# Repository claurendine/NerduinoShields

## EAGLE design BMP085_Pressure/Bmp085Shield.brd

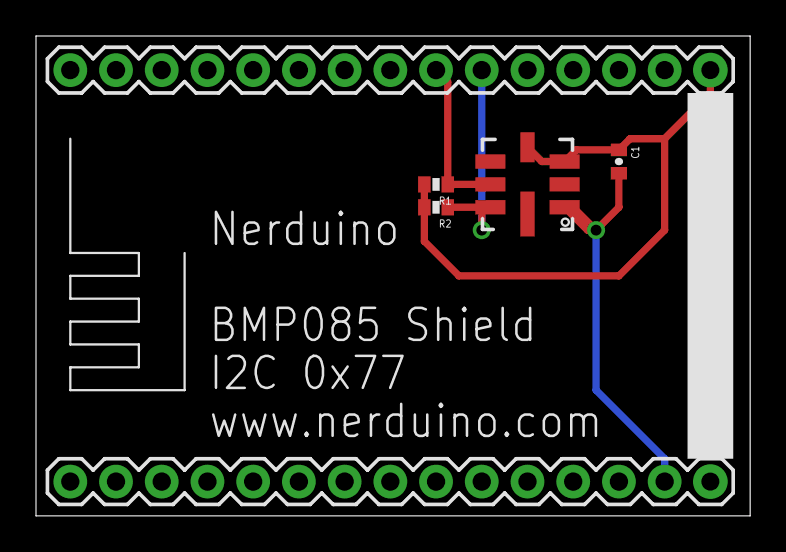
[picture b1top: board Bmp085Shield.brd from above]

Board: 2 copper layers, 39.7 x 26.7 mm, 5 parts (0 on the bottom side), 4 nets.

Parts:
C1: 0.1uF; 0402-CAP
R1, R2: 4.7k; 0402-RES
U$1: NERDSHIELD; NERDUINO_STACK
U$2: BMP085

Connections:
3.3V: C1.1, R1.2, R2.2, U$1.16, U$2.3, U$2.4
GND: C1.2, U$1.14, U$2.1
unnamed: R2.1, U$1.21, U$2.7
unnamed: R1.1, U$1.22, U$2.6

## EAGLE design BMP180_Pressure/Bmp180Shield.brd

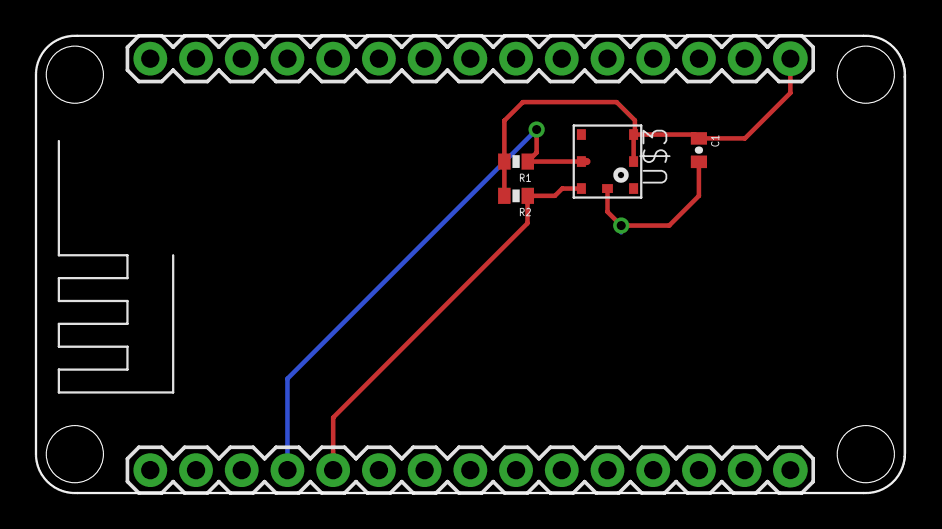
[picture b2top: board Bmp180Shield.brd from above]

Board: 2 copper layers, 48.3 x 25.4 mm, 5 parts (0 on the bottom side), 4 nets.

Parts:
C1: 0.1uF; 0402-CAP
R1, R2: 4.7k; 0402-RES
U$1: NERDSHIELD; NERDUINO_STACK
U$3: BMP180

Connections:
3.3V: C1.1, R1.2, R2.2, U$1.16, U$3.2, U$3.3
GND: C1.2, U$1.10, U$1.14, U$1.17, U$3.7
unnamed: R2.1, U$1.5, U$3.6
unnamed: R1.1, U$1.4, U$3.5

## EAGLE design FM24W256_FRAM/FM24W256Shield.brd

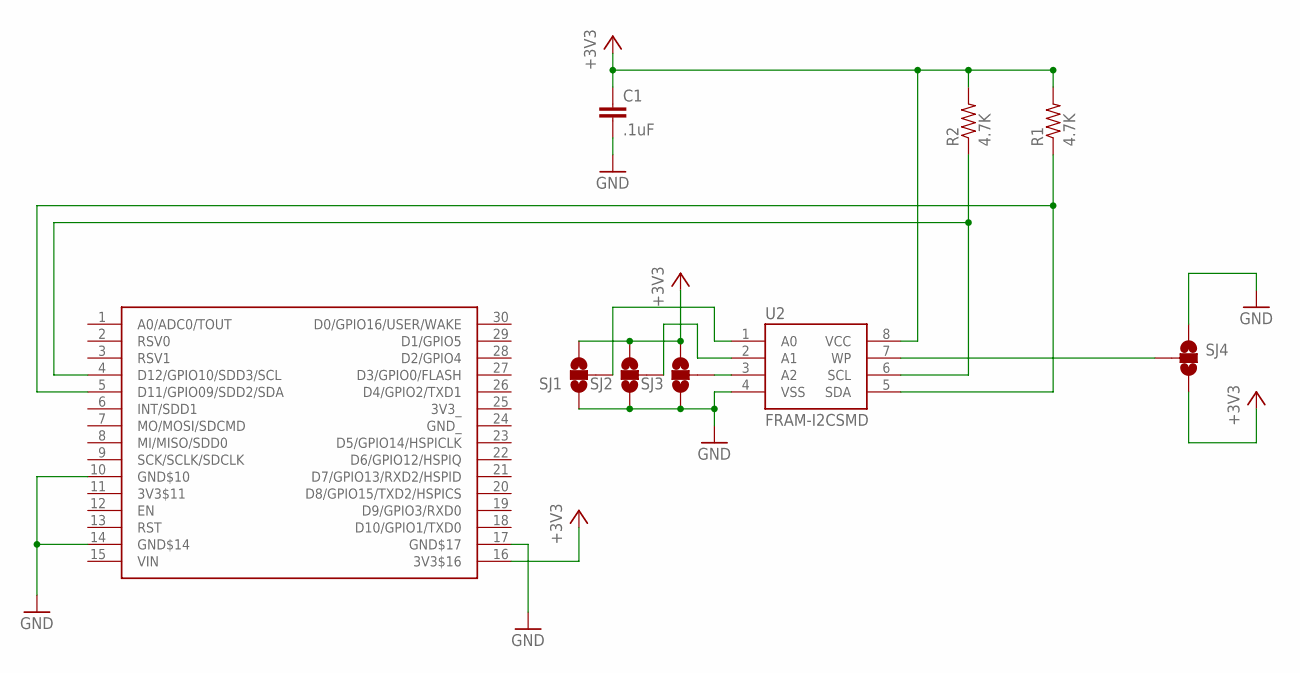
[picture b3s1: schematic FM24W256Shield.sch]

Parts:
C1: .1uF; 0603-CAP
R1, R2: 4.7K; 0603-RES
SJ1, SJ2, SJ3, SJ4: SOLDERJUMPER_2WAYPASTE1&2; SJ_3_PASTE1&2
U2: FRAM-I2CSMD; SO08
U$2: NERDSHIELD; NERDUINO_STACK

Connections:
+3V3: C1.1, R1.2, R2.2, SJ1.3, SJ2.3, SJ3.3, SJ4.3, U2.8 (VCC), U$2.16 (3V3$16)
GND: C1.2, SJ1.1, SJ2.1, SJ3.1, SJ4.1, U2.4 (VSS), U$2.10 (GND$10), U$2.14 (GND$14), U$2.17 (GND$17)
unnamed: R1.1, U2.5 (SDA), U$2.5 (D11/GPIO09/SDD2/SDA)
unnamed: SJ3.2, U2.3 (A2)
unnamed: R2.1, U2.6 (SCL), U$2.4 (D12/GPIO10/SDD3/SCL)
unnamed: SJ2.2, U2.2 (A1)
unnamed: SJ1.2, U2.1 (A0)
unnamed: SJ4.2, U2.7 (WP)

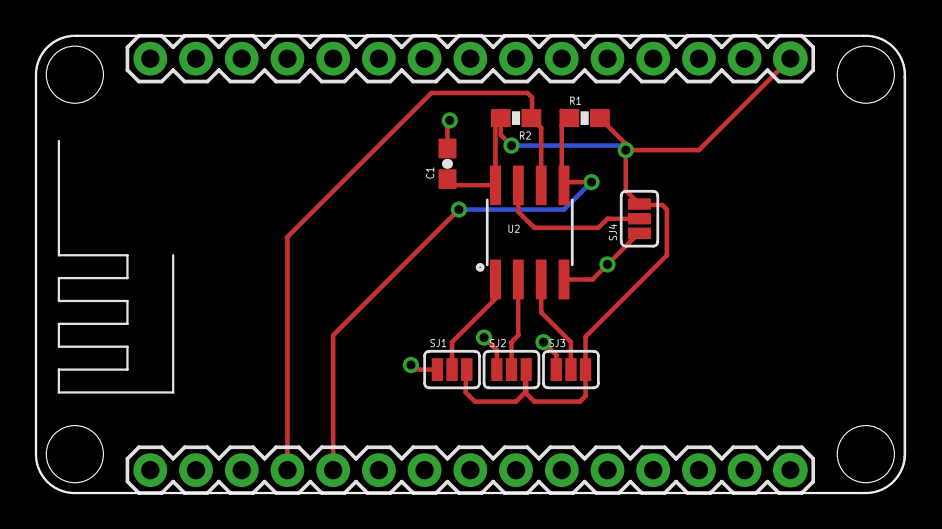
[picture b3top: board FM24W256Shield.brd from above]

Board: 2 copper layers, 48.3 x 25.4 mm, 9 parts (0 on the bottom side), 8 nets.

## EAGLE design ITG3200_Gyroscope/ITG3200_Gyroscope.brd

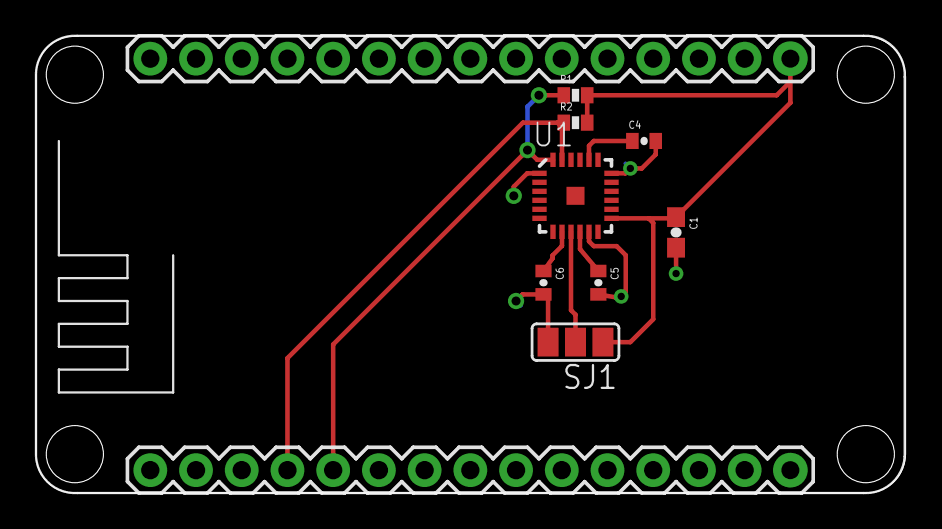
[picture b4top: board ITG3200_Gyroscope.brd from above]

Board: 2 copper layers, 48.3 x 25.4 mm, 9 parts (0 on the bottom side), 8 nets.

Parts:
C1: .1uF; 0603-CAP
C4: 2.2nF; 0402-CAP
C5: .1uF; 0402-CAP
C6: 10nF; 0402-CAP
R1, R2: 4.7K; 0402-RES
SJ1: SJ_2
U1: ITG-3200; QFN-24
U$2: NERDSHIELD; NERDUINO_STACK

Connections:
+3V3: C1.1, R1.2, R2.2, SJ1.1, U1.13, U$2.16
GND: C1.2, C4.2, C5.2, C6.2, SJ1.3, U1.1, U1.11, U1.18, U$2.10, U$2.14, U$2.17
unnamed: SJ1.2, U1.9
unnamed: R1.1, U1.24, U$2.5
unnamed: R2.1, U1.23, U$2.4
unnamed: C4.1, U1.20
unnamed: C5.1, U1.10
unnamed: C6.1, U1.8

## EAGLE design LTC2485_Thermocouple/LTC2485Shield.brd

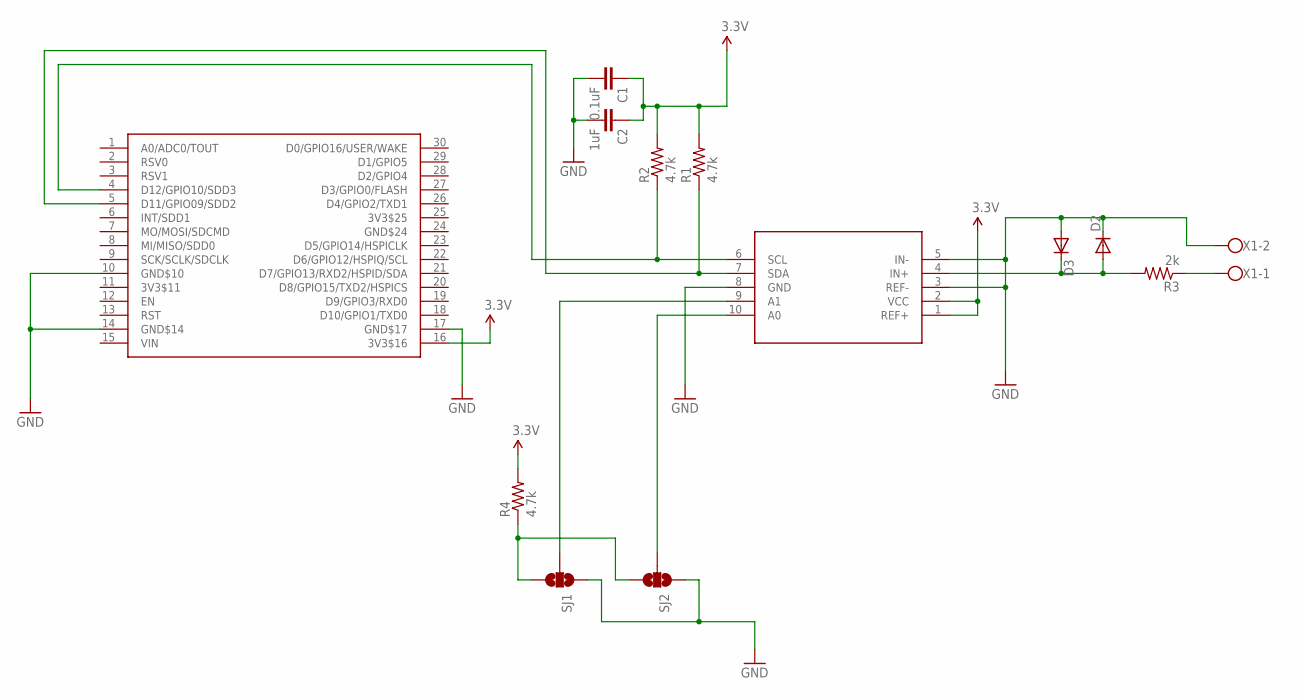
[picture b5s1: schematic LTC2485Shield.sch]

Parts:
C1: 0.1uF; 0402-CAP
C2: 1uF; 0402-CAP
D2, D3: DIODESOD; SOD-323
R1, R2, R4: 4.7k; 0402-RES
R3: 2k; 0402-RES
SJ1, SJ2: SOLDERJUMPER_2WAYT; SJ_2
U$1: NERDSHIELD; NERDUINO_STACK
U$2: LTC2485; DFN10-3X3
X1: W237-102

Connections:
3.3V: C1.1, C2.1, R1.2, R2.2, R4.2, U$1.16 (3V3$16), U$2.1 (REF+), U$2.2 (VCC)
GND: C1.2, C2.2, D2.1 (C), D3.2 (A), SJ1.1, SJ2.1, U$1.10 (GND$10), U$1.14 (GND$14), U$1.17 (GND$17), U$2.3 (REF-), U$2.5 (IN-), U$2.8 (GND), X1.2
unnamed: R3.1, X1.1
unnamed: R1.1, U$1.5 (D11/GPIO09/SDD2), U$2.7 (SDA)
unnamed: D2.2 (A), D3.1 (C), R3.2, U$2.4 (IN+)
unnamed: R4.1, SJ1.3, SJ2.3
unnamed: SJ1.2, U$2.9 (A1)
unnamed: R2.1, U$1.4 (D12/GPIO10/SDD3), U$2.6 (SCL)
unnamed: SJ2.2, U$2.10 (A0)

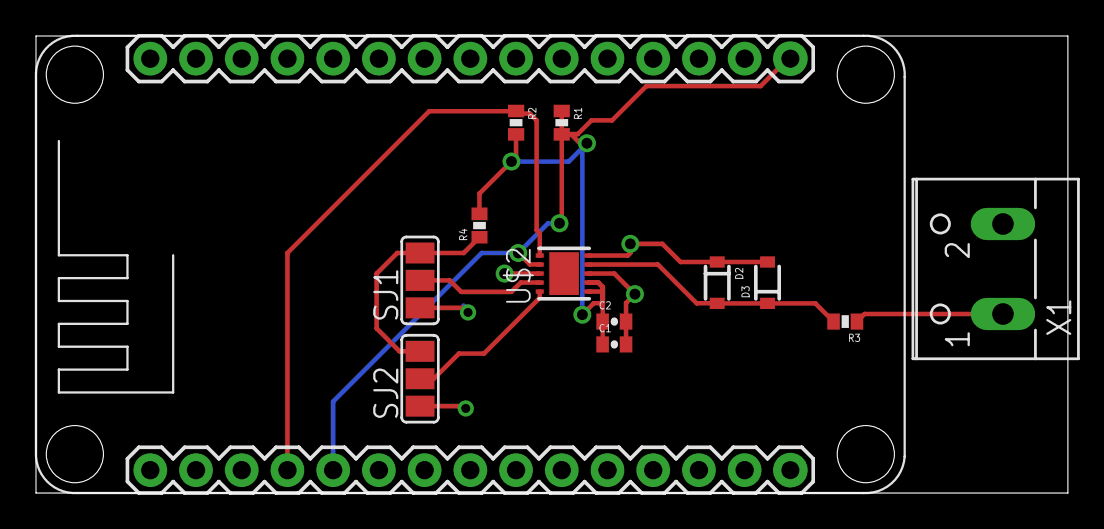
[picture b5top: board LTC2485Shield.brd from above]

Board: 2 copper layers, 57.3 x 25.4 mm, 13 parts (0 on the bottom side), 9 nets.

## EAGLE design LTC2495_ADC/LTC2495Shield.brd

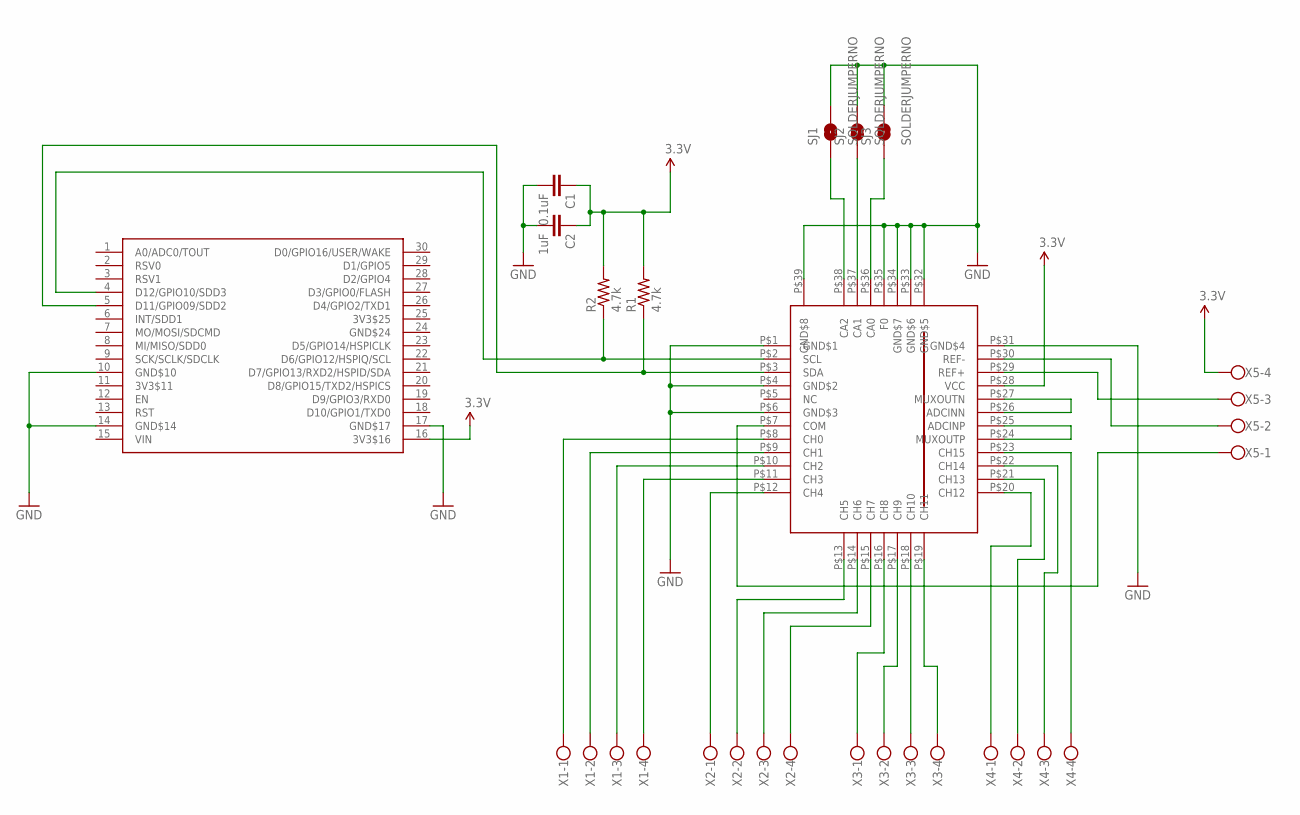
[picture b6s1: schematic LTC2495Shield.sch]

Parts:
C1: 0.1uF; 0402-CAP
C2: 1uF; 0402-CAP
R1, R2: 4.7k; 0402-RES
SJ1, SJ2, SJ3: SOLDERJUMPERNO; SJ_2S-NO
U$1: NERDSHIELD; NERDUINO_STACK
U$3: LTC2495; UHF38
X1, X2, X3, X4, X5: W237-4

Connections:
3.3V: C1.1, C2.1, R1.2, R2.2, U$1.16 (3V3$16), U$3.P$28 (VCC), X5.4
GND: C1.2, C2.2, SJ1.2, SJ2.2, SJ3.2, U$1.10 (GND$10), U$1.14 (GND$14), U$1.17 (GND$17), U$3.P$1 (GND$1), U$3.P$4 (GND$2), U$3.P$6 (GND$3), U$3.P$31 (GND$4), U$3.P$32 (GND$5), U$3.P$33 (GND$6), U$3.P$34 (GND$7), U$3.P$35 (F0), U$3.P$39 (GND$8)
unnamed: R1.1, U$1.5 (D11/GPIO09/SDD2), U$3.P$3 (SDA)
unnamed: U$3.P$8 (CH0), X1.1
unnamed: U$3.P$9 (CH1), X1.2
unnamed: U$3.P$10 (CH2), X1.3
unnamed: U$3.P$11 (CH3), X1.4
unnamed: U$3.P$12 (CH4), X2.1
unnamed: R2.1, U$1.4 (D12/GPIO10/SDD3), U$3.P$2 (SCL)
unnamed: U$3.P$13 (CH5), X2.2
unnamed: U$3.P$14 (CH6), X2.3
unnamed: U$3.P$15 (CH7), X2.4
unnamed: U$3.P$16 (CH8), X3.1
unnamed: U$3.P$17 (CH9), X3.2
unnamed: U$3.P$18 (CH10), X3.3
unnamed: U$3.P$19 (CH11), X3.4
unnamed: U$3.P$20 (CH12), X4.1
unnamed: U$3.P$21 (CH13), X4.2
unnamed: U$3.P$22 (CH14), X4.3
unnamed: U$3.P$23 (CH15), X4.4
unnamed: SJ1.1, U$3.P$38 (CA2)
unnamed: SJ2.1, U$3.P$37 (CA1)
unnamed: SJ3.1, U$3.P$36 (CA0)
unnamed: U$3.P$7 (COM), X5.1
unnamed: U$3.P$29 (REF+), X5.3
unnamed: U$3.P$30 (REF-), X5.2
unnamed: U$3.P$26 (ADCINN), U$3.P$27 (MUXOUTN)
unnamed: U$3.P$24 (MUXOUTP), U$3.P$25 (ADCINP)

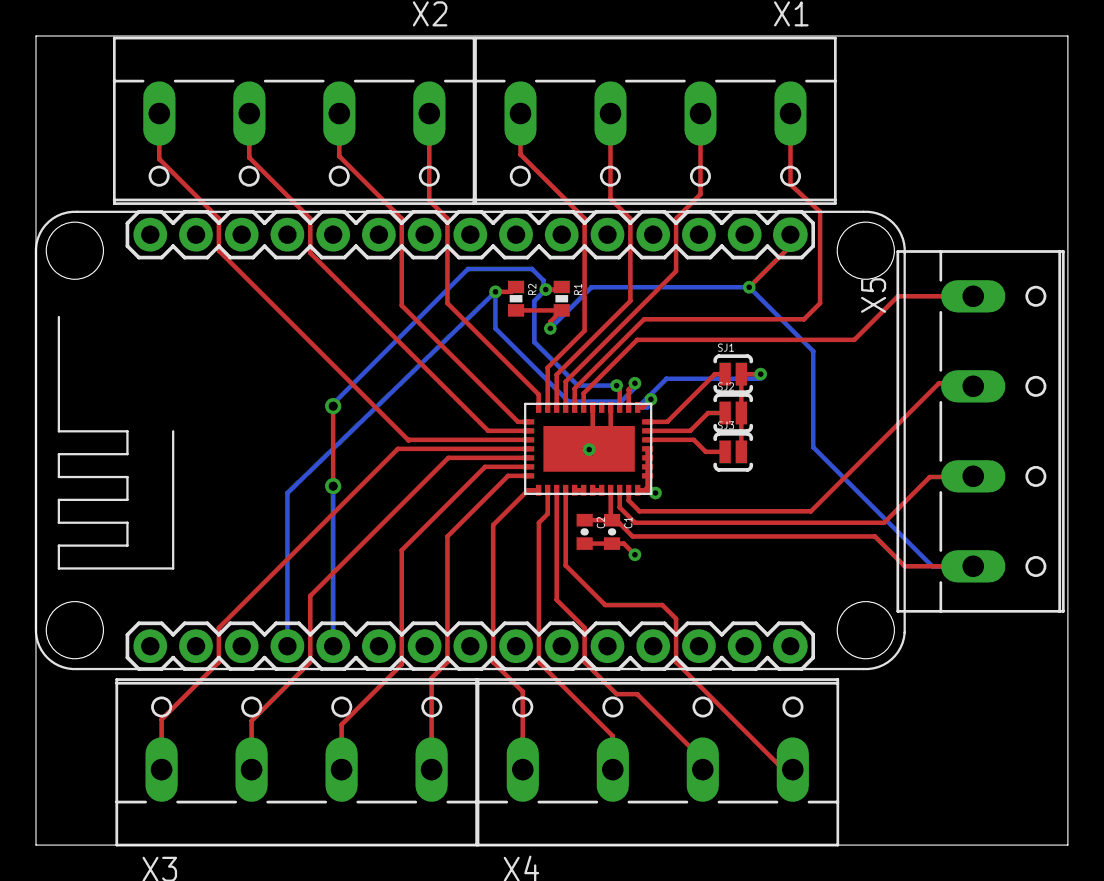
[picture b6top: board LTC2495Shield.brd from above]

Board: 2 copper layers, 57.3 x 44.9 mm, 14 parts (0 on the bottom side), 28 nets.

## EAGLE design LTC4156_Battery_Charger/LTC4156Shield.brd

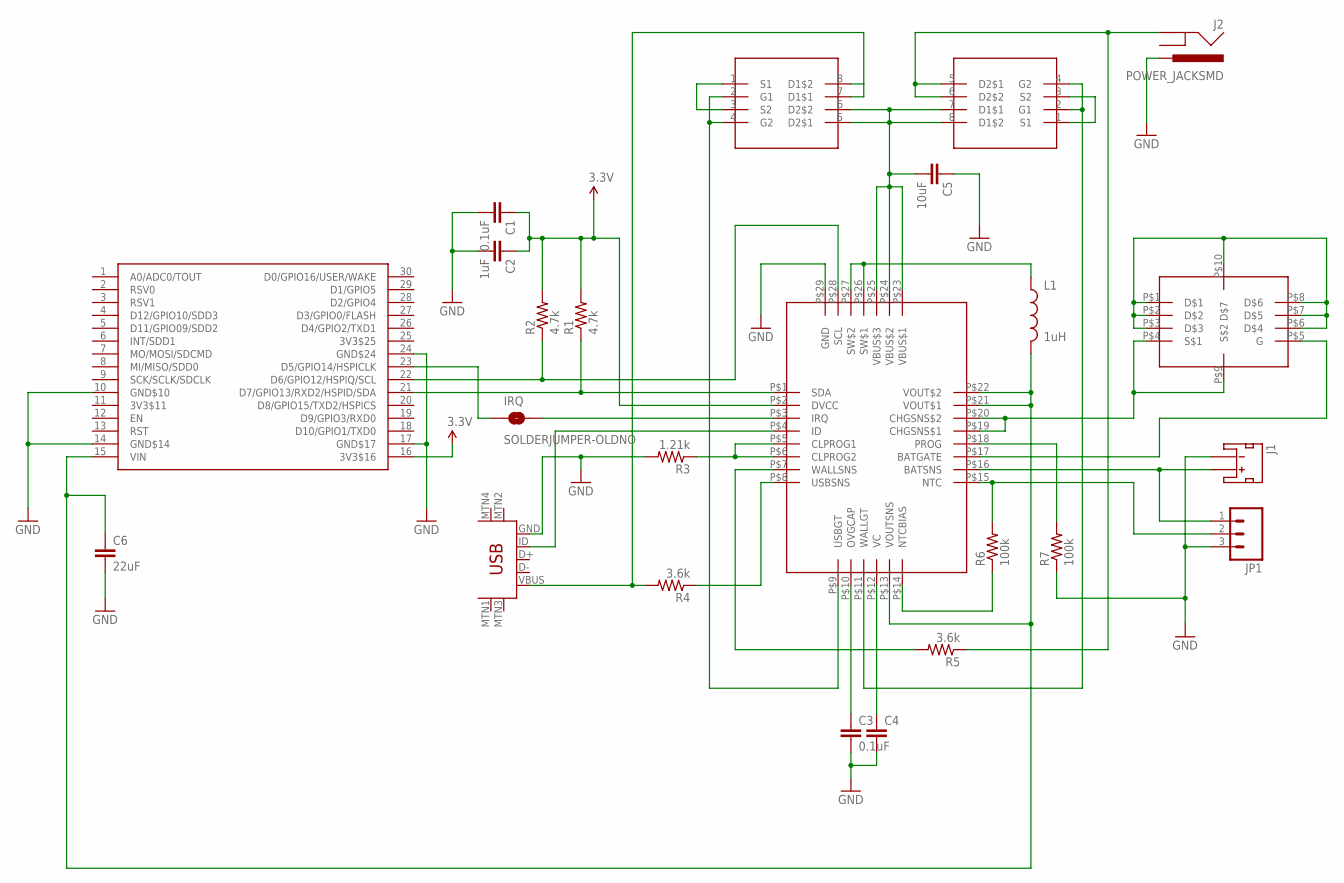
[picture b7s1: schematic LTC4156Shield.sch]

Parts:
C1, C3: 0.1uF; 0402-CAP
C2: 1uF; 0402-CAP
C4: CAP0805; 0805
C5: 10uF; 0402-CAP
C6: 22uF; 0402-CAP
IRQ: SOLDERJUMPER-OLDNO; SJ_2S-NO
J1: JST_2MM_MALE; JST-2-SMD
J2: POWER_JACKSMD; POWER_JACK_SMD
JP1: M03; JST-3-SMD
L1: 1uH; 0805
R1, R2: 4.7k; 0402-RES
R3: 1.21k; 0402-RES
R4, R5: 3.6k; 0402-RES
R6, R7: 100k; 0402-RES
U$1: NERDSHIELD; NERDUINO_STACK
U$2: LTC4156; QFN28
U$3, U$5: SI7938DP; SO08
U$4: USB-MINIB-5PIN; USB-MINIB
U$6: SI5481

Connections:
3.3V: C1.1, C2.1, R1.2, R2.2, U$1.16 (3V3$16), U$2.P$2 (DVCC)
GND: C1.2, C2.2, C3.2, C4.2, C5.1, C6.2, J1.1 (-), J2.VIN0 (PWR), JP1.3, R3.2, R7.1, U$1.10 (GND$10), U$1.14 (GND$14), U$1.17 (GND$17), U$1.24 (GND$24), U$2.P$29 (GND), U$4.GND
unnamed: R4.1, U$2.P$8 (USBSNS)
unnamed: R1.1, U$1.21 (D7/GPIO13/RXD2/HSPID/SDA), U$2.P$1 (SDA)
unnamed: IRQ.2, U$2.P$3 (IRQ)
unnamed: R3.1, U$2.P$5 (CLPROG1), U$2.P$6 (CLPROG2)
unnamed: IRQ.1, U$1.23 (D5/GPIO14/HSPICLK)
unnamed: U$2.P$4 (ID), U$4.ID
unnamed: R4.2, U$3.7 (D1$1), U$3.8 (D1$2), U$4.VBUS
unnamed: R2.1, U$1.22 (D6/GPIO12/HSPIQ/SCL), U$2.P$28 (SCL)
unnamed: U$2.P$9_ (USBGT), U$3.2 (G1), U$3.4 (G2)
unnamed: C5.2, U$2.P$23 (VBUS$1), U$2.P$24 (VBUS$2), U$2.P$25 (VBUS$3), U$3.5 (D2$1), U$3.6 (D2$2), U$5.7 (D1$1), U$5.8 (D1$2)
unnamed: R5.2, U$2.P$7 (WALLSNS)
unnamed: U$3.1 (S1), U$3.3 (S2)
unnamed: U$5.1 (S1), U$5.3 (S2)
unnamed: U$2.P$11_ (WALLGT), U$5.2 (G1), U$5.4 (G2)
unnamed: J2.P$4 (GND), R5.1, U$5.5 (D2$1), U$5.6 (D2$2)
unnamed: C3.1, U$2.P$10_ (OVGCAP)
unnamed: C4.1, U$2.P$12_ (VC)
unnamed: C6.1, L1.2, U$1.15 (VIN), U$2.P$13_ (VOUTSNS), U$2.P$21 (VOUT$1), U$2.P$22 (VOUT$2)
unnamed: J1.2 (+), JP1.1, U$2.P$16 (BATSNS)
unnamed: L1.1, U$2.P$26 (SW$1), U$2.P$27 (SW$2)
unnamed: JP1.2, R6.2, U$2.P$15 (NTC)
unnamed: R6.1, U$2.P$14_ (NTCBIAS)
unnamed: U$2.P$17 (BATGATE), U$6.P$5 (G)
unnamed: U$2.P$19 (CHGSNS$1), U$2.P$20 (CHGSNS$2), U$6.P$4, U$6.P$9
unnamed: U$6.P$1, U$6.P$2, U$6.P$3, U$6.P$6, U$6.P$7, U$6.P$8, U$6.P$10
unnamed: R7.2, U$2.P$18 (PROG)

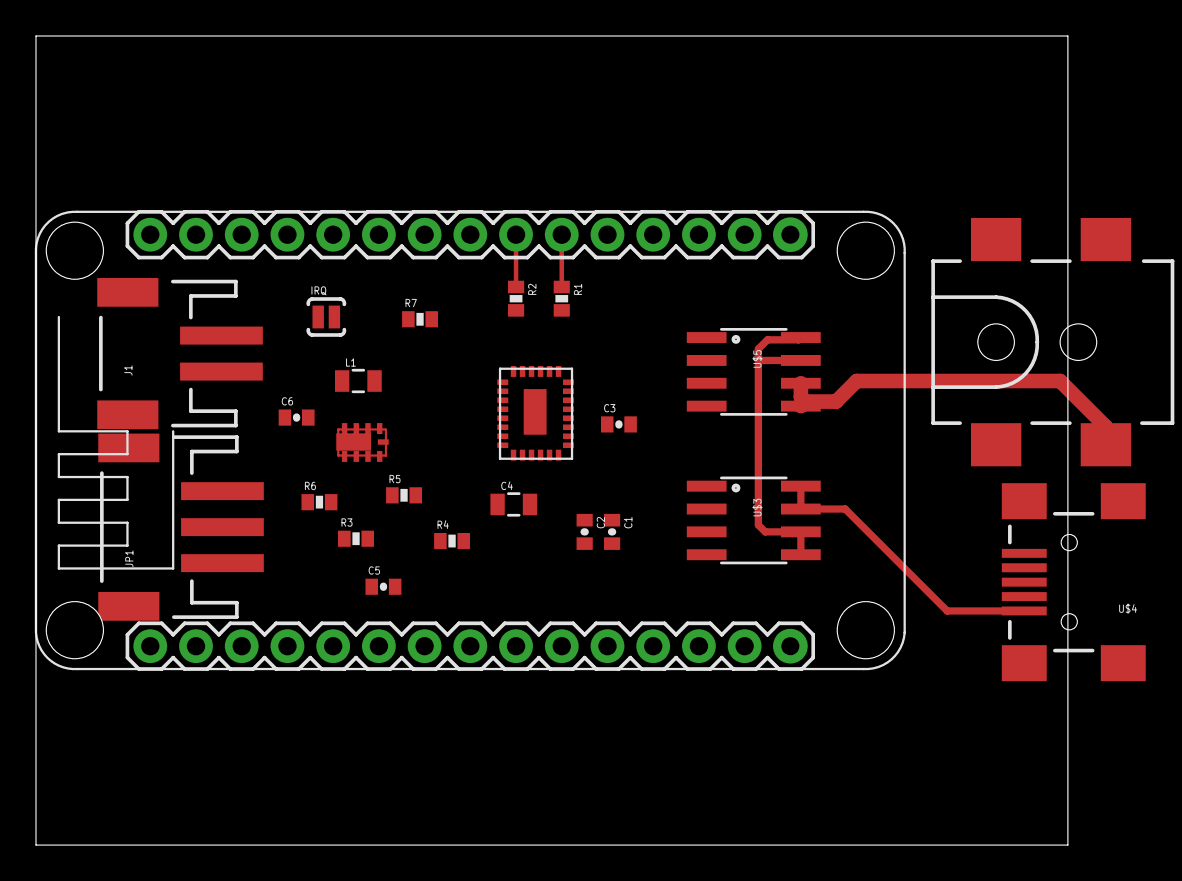
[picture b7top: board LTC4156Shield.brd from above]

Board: 2 copper layers, 57.3 x 44.9 mm, 24 parts (0 on the bottom side), 28 nets.

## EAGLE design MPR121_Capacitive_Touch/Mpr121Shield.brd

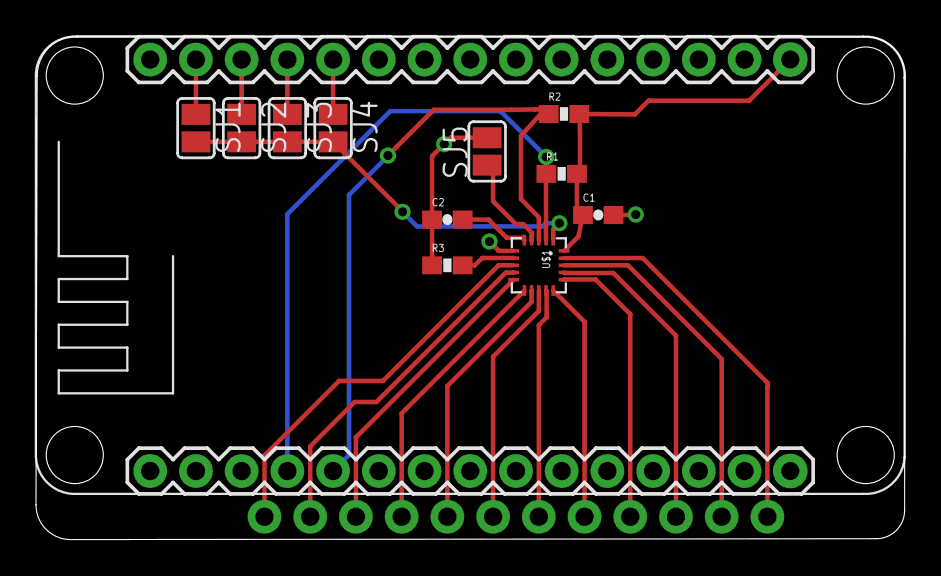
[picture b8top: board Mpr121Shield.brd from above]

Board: 2 copper layers, 48.3 x 28.0 mm, 13 parts (0 on the bottom side), 24 nets.

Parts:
C1, C2: .1uF; 0603-CAP
JP3: 1X12_NO_SILK
R1, R2, R3: 4.7K; 0603-RES
SJ1, SJ2, SJ3, SJ4, SJ5: SJ
U$1: MPR121QFN20; QFN-20-0.4MM
U$2: NERDSHIELD; NERDUINO_STACK

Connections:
+3V3: C1.1, R1.2, R2.2, U$1.20, U$2.16
GND: C1.2, C2.1, R3.1, SJ5.2, U$1.6, U$2.10, U$2.14, U$2.17
unnamed: JP3.1, U$1.19
unnamed: R1.1, U$1.2, U$2.4
unnamed: JP3.2, U$1.18
unnamed: R2.1, U$1.3, U$2.5
unnamed: JP3.3, U$1.17
unnamed: JP3.4, U$1.16
unnamed: JP3.5, U$1.15
unnamed: JP3.6, U$1.14
unnamed: JP3.7, U$1.13
unnamed: JP3.8, U$1.12
unnamed: JP3.9, U$1.11
unnamed: JP3.10, U$1.10
unnamed: JP3.11, U$1.9
unnamed: JP3.12, U$1.8
unnamed: C2.2, U$1.5
unnamed: R3.2, U$1.7
unnamed: SJ5.1, U$1.4
unnamed: SJ1.2, SJ2.2, SJ3.2, SJ4.2, U$1.1
unnamed: SJ1.1, U$2.29
unnamed: SJ2.1, U$2.28
unnamed: SJ3.1, U$2.27
unnamed: SJ4.1, U$2.26

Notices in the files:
parts and their libraries:
SparkFun: Licensing: CC v3.0 Share-Alike You are welcome to use this library for commercial purposes.
SparkFun-Sensors: Licensing: Creative Commons ShareAlike 4.0 International - https://creativecommons.org/licenses/by-sa/4.0
